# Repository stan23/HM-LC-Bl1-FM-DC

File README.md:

# HM-LC-Bl1-FM-DC          
Nachbau HM-LC-Bl1-FM Rollladenaktor für Gleichstrommotoren (z.B. Plissee)

Er verhält sich wie ein Rolloaktor, treibt aber einen 12/24 V Gleichstrommotor. Dieser wird je nach Fahrtrichtung umgepolt.

Dies basiert auf der hervorragenden Arbeit von [pa-pa](https://github.com/pa-pa/AskSinPP),  [Jérôme](https://github.com/jp112sdl/Beispiel_AskSinPP) und micha68.

[Link zur neueren Version der Platine](https://github.com/stan23/myPCBs/tree/master/HM-LC-Bl1-FM-DC)

## Hardware

### Bauteile

#### Reichelt

[Bestellliste](https://www.reichelt.de/my/1495010)

Bauteil                  | Bestellnummer   | Anzahl | Kommentar
------------------------ | --------------- | ------ | ---------
C6                       | X5R-G0603 10/6  |   1    | -
C1, C2, C3, C8, C21, C22 | X7R-G0603 100N  |   6    | -
C7                       | TAJ 3528 3,3/35 |   1    |  -
R22, R24                 | RND 0603 1 47   |   1    | -
R2                       | RND 0603 1 1,5K |   2    | -
R11, R12                 | RND 0603 1 2,7K |   2    | -
R1, R21, R23             | RND 0603 1 10K  |   3    | -
D1                       | SLO SMD-Y0603-0 |   1    | -
D2, D11, D12             | 1N 4148 WS      |   3    | -
Q1, Q2                   | BC 817 NXP      |   2    | -
U1                       | ATMEGA 328P-AU  |   1    | -
U3                       | SIM1-2403 SIL4  |   1    | für 24 V
U3                       | SIM1-1203 SIL4  |   1    | alternativ für 12 V
K1, K2                   | G6S-2 24V       |   2    | für 24 V
K1, K2                   | G6S-2 12V       |   2    | alternativ für 12 V
X1                       | WAGO 250-204    |   1    | -
X2                       | WAGO 250-404    |   1    | siehe [Issue #1](https://github.com/stan23/HM-LC-Bl1-FM-DC/issues/1)
Verbinder zu U2          | SL 1X20G 2,00   |   1    | -
Verbinder zu U2          | MPE 156-1-032   |   1    | optional

#### Sonstiges

Bauteil | Bestellnummer            | Anzahl | Kommentar
------- | ------------------------ | ------ | ---------
U2      | CC1101 Funkmodul 868MHz  |   1    | z.B. [eBay](https://www.ebay.de/itm/272455136087)

### Programmieradapter
- 1x ISP (um den Bootloader zu brennen)
- 1x FTDI Adapter (falls nicht schon vorhanden, gibts bei [Amazon](https://www.amazon.de/FT232RL-FTDI-USB-auf-TTL-Serienadapter-Arduino/dp/B00HSXDGOE))

## Software

### Fuses

Low:  0xE2
High: 0xD2
Ext:  0xFF

### Bootloader

Aus der Arduino IDE, für ATmega328P, 3,3 V, 8 MHz

### Firmware

https://github.com/pa-pa/AskSinPP/tree/master/examples/HM-LC-Bl1-FM

## Bilder

.jpg)
.jpg)
.jpg)
.jpg)
.jpg)

Dieses Werk ist lizenziert unter einer [Creative Commons Namensnennung - Nicht-kommerziell - Weitergabe unter gleichen Bedingungen 4.0 International Lizenz](http://creativecommons.org/licenses/by-nc-sa/4.0/).

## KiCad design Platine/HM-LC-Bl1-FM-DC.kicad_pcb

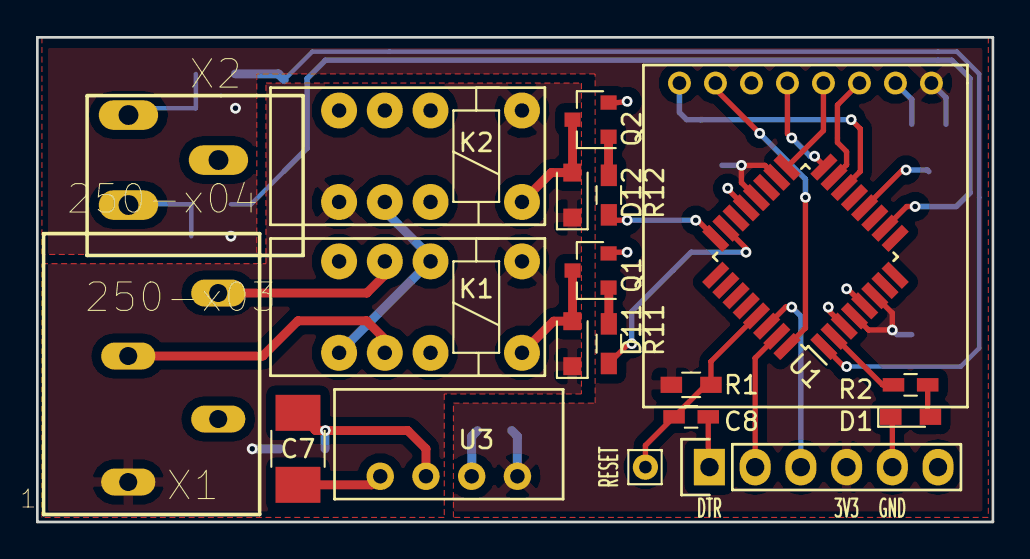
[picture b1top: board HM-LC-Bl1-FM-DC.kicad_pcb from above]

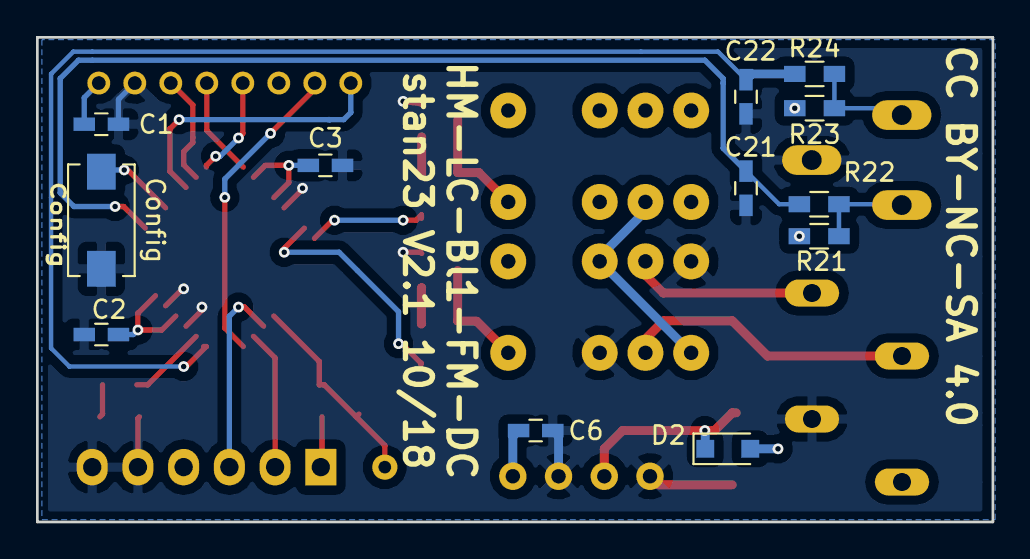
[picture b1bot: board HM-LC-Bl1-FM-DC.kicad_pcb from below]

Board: 2 copper layers, 53.1 x 26.9 mm, 32 parts (12 on the bottom side), 29 nets.

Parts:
C1, C2, C3, C8, C21, C22: 100n; C_0603_HandSoldering
C6: 10u; C_0603_HandSoldering
C7: 3.3u 35V; C_1210_HandSoldering
D1: LED_Rot; LED_0603_HandSoldering
D2, D11, D12: 1N4148; D_SOD-323_HandSoldering
J2: FTDI; Pin_Header_Straight_1x06
J4: Reset; Pin_d0.7mm_L6.5mm_W1.8mm_FlatFork
K1, K2: OMRONG6S-2; Relay_Omron_G6S-2
Q1, Q2: BC817; SOT-23
R1, R21, R23: 10k; R_0603_HandSoldering
R2: 1k5; C_0603_HandSoldering
R11, R12: 2k7; R_0603_HandSoldering
R22, R24: 47; R_0603_HandSoldering
SW2: Config; SW_SPST_EVQPE1
U1: ATMEGA328P-AU; TQFP-32_7x7mm_Pitch0.8mm
U2: CC1101; CC1101_Module
U3: AM1S-2403S; SIL-4
X1: 250-x04; P-250-204
X2: 250-x03; P-250-403

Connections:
+24V: D2.2, D11.1, D12.1, K1.1, K2.1, K2.8, X1.L1
/C0: R11.2, U1.23
/C1: R12.2, U1.24
/D3: C22.1, R24.1, U1.1
/D6: C21.1, R22.1, U1.10
/DOWN: R23.1, R24.2, X2.L1
/DTR: C8.1, J2.1
/MISO: U1.16, U2.5
/MOSI: U1.15, U2.3
/Motor1: K1.9, X1.L3
/Motor2: K1.4, X1.L4
/RXD: J2.3, U1.30
/Reset: C8.2, J4.1, R1.2, U1.29
/SCK: U1.17, U2.4
/TXD: J2.2, U1.31
/UP: R21.1, R22.2, X2.L3
GND: C1.2, C2.2, C3.2, C6.2, C7.2, C21.2, C22.2, D1.1, J2.5, J2.6, K1.5, K1.10, Q1.2, Q2.2, SW2.1, U1.3, U1.5, U1.21, U2.2, U3.1, U3.3, X1.L2, X2.L2
unnamed: C7.1, D2.1, U3.2
unnamed: D1.2, R2.2
unnamed: D11.2, K1.12, Q1.3
unnamed: D12.2, K2.12, Q2.3
unnamed: K1.3, K1.8, K2.9
unnamed: Q1.1, R11.1
unnamed: Q2.1, R12.1
unnamed: R2.1, U1.2
unnamed: SW2.2, U1.12
unnamed: U1.14, U2.8
unnamed: U1.32, U2.7
VCC: C1.1, C2.1, C3.1, C6.1, J2.4, R1.1, R21.2, R23.2, U1.4, U1.6, U1.18, U1.20, U2.1, U3.4

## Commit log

2018-08-08 add PDFs
2018-08-08 add KiCad files
2018-08-08 add libraries
2018-08-08 update schematic to include the values
2018-08-13 add pictures
2018-08-14 link pictures to Readme
2018-09-02 add license link
2018-10-18 update to 2.1
    fix mirrored footprint of X2
2019-07-22 alternate placement for 12 V supply
2024-07-20 link newer version

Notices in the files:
Platine/HM-LC-Bl1-FM-DC.kicad_pcb:
CC BY-NC-SA 4.0
README.md:
License: CC BY-NC-SA 4.0
Creative Commons Lizenzvertrag
